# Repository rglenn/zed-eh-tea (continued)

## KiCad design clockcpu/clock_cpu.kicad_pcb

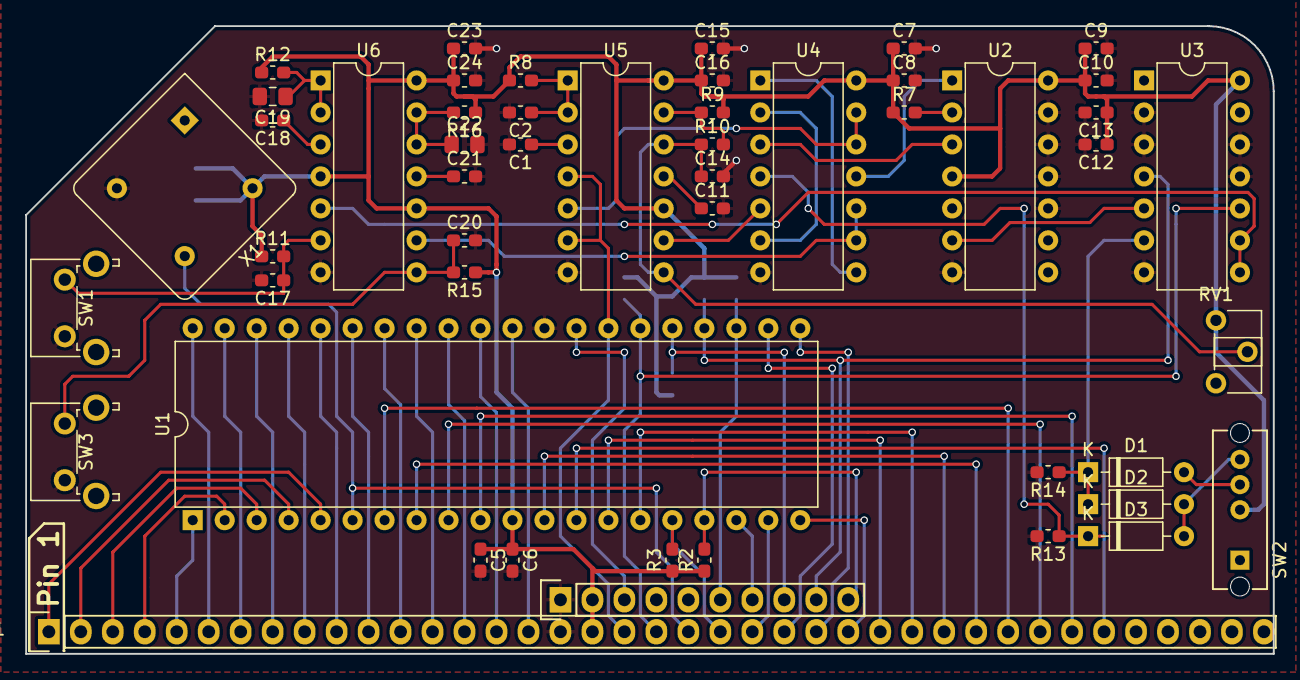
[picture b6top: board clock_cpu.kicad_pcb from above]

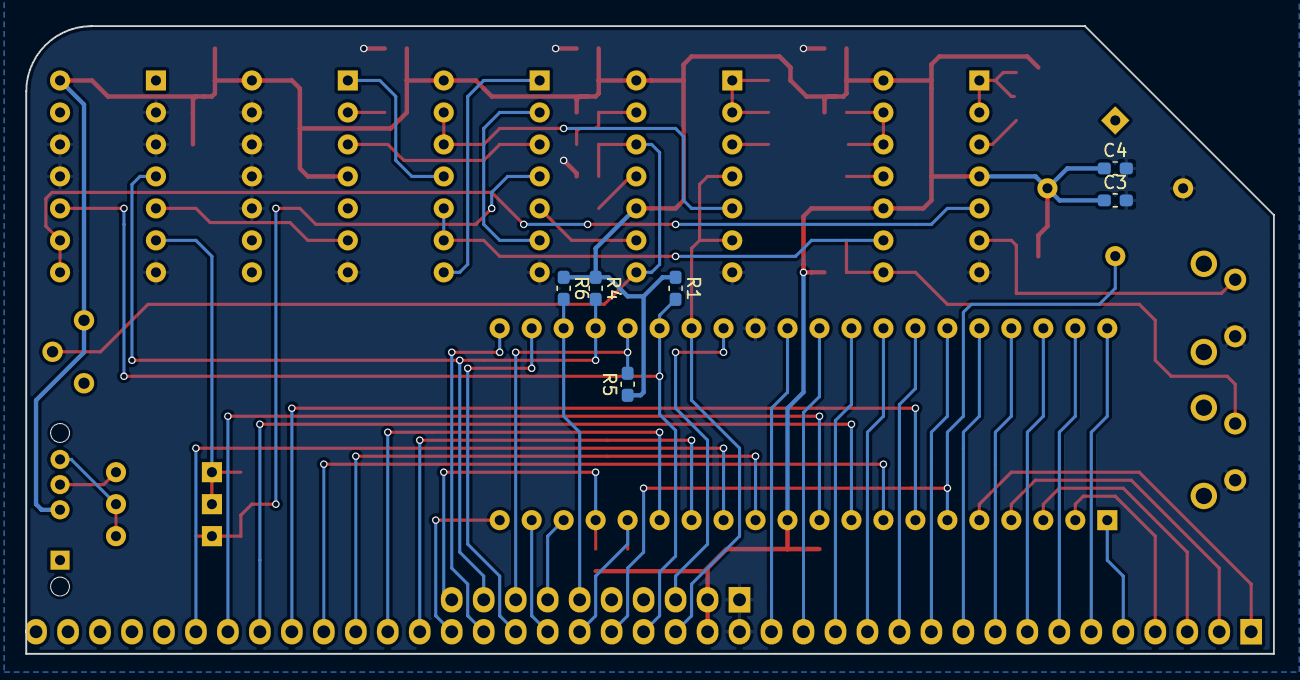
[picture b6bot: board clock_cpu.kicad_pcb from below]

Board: 2 copper layers, 99.1 x 49.9 mm, 56 parts (6 on the bottom side), 65 nets.

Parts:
C1, C2, C11, C18, C21: 10n; C_0603_1608Metric_Pad1.05x0.95mm_HandSolder
C3, C5, C7, C9, C12, C14, C15, C23: 1u; C_0603_1608Metric_Pad1.05x0.95mm_HandSolder
C4, C6, C8, C10, C13, C16, C17, C20, C24: 100n; C_0603_1608Metric_Pad1.05x0.95mm_HandSolder
C19, C22: 10u; C_0805_2012Metric_Pad1.15x1.40mm_HandSolder
D1, D2, D3: 1N4148; D_DO-35_SOD27_P7.62mm_Horizontal
J1: CONN_01X39; Pin_Header_Straight_1x39_Pitch2.54mm
J2: CONN_01X10; Pin_Header_Straight_1x10_Pitch2.54mm
R1, R2, R3, R4, R5, R6, R7, R8, R9, R10, R12, R13, R14, R16: 10K; R_0603_1608Metric_Pad1.05x0.95mm_HandSolder
R11, R15: 47K; R_0603_1608Metric_Pad1.05x0.95mm_HandSolder
RV1: 500K; Potentiometer_Piher_PT-6-H_Horizontal
SW1, SW3: SW_Push; SW_Tactile_SPST_Angled_PTS645Vx31-2LFS
SW2: SW_SP3T; OS103011MA7QP1
U1: Z80CPU; DIP-40_W15.24mm
U2: 74HCT74; DIP-14_W7.62mm
U3: 74HCT01; DIP-14_W7.62mm
U4: 74AHCT132; DIP-14_W7.62mm
U5, U6: LM556; DIP-14_W7.62mm
X1: CXO_DIP8; Oscillator_DIP-8

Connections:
/BUSACK: J2.6, R6.2, U1.23
/BUSREQ: J2.8, R5.2, U1.25
/ENABLE_AUTOSTEP: D3.1, R13.1, U4.4
/ENABLE_STEP: D1.1, D2.1, R14.1, U3.6
/HALT: J2.7, U1.18
/IORQ: J1.26, U1.20
/M1: J1.19, U1.27, U5.4, U5.6
/MREQ: J1.23, U1.19
/NMI: J2.10, R2.2, U1.17
/RD: J1.25, U1.21
/RFSH: J2.3, U1.28
/RST: J1.20, R1.2, U1.26, U3.10
/STEP_BTN: U4.1, U4.8
/STEP_CLK: U2.3, U4.3
/WAIT: J2.9, R4.2, U1.24, U3.4
/WR: J1.24, U1.22
A0: J1.16, U1.30
A1: J1.15, U1.31
A2: J1.14, U1.32
A3: J1.13, U1.33
A4: J1.12, U1.34
A5: J1.11, U1.35
A6: J1.10, U1.36
A7: J1.9, U1.37
A8: J1.8, U1.38
A9: J1.7, U1.39
A10: J1.6, U1.40
A11: J1.5, U1.1
A12: J1.4, U1.2
A13: J1.3, U1.3
A14: J1.2, U1.4
A15: J1.1, U1.5
CLK: J1.21, U1.6, X1.5
D0: J1.27, U1.14
D1: J1.28, U1.15
D2: J1.29, U1.12
D3: J1.30, U1.8
D4: J1.31, U1.7
D5: J1.32, U1.9
D6: J1.33, U1.10
D7: J1.34, U1.13
GND: C1.2, C2.2, C3.2, C4.2, C5.2, C6.2, C7.2, C8.2, C9.2, C10.2, C11.2, C12.2, C13.2, C14.2, C15.2, C16.2, C17.2, C18.2, C19.2, C20.2, C21.2, C22.2, C23.2, C24.2, J1.17, J2.1, R13.2, R14.2, SW1.1, SW3.1, U1.29, U2.7, U2.10, U2.11, U2.12, U2.13, U3.2, U3.3, U3.7, U3.11, U3.12, U4.7, U5.7, U6.7, X1.4
INT: J1.22, R3.2, U1.16
unnamed: C1.1, U5.3
unnamed: C2.1, R8.2, U5.1, U5.2
unnamed: C11.1, U5.11
unnamed: C14.1, R10.1, RV1.2, U5.8, U5.12
unnamed: C17.1, R11.2, SW1.2, U6.6
unnamed: C18.1, U6.3
unnamed: C19.1, R12.2, U6.1, U6.2
unnamed: C20.1, R15.2, SW3.2, U6.8
unnamed: C21.1, U6.11
unnamed: C22.1, R16.2, U6.12, U6.13
unnamed: D1.2, SW2.2
unnamed: D2.2, D3.2, SW2.4
unnamed: R7.2, U2.2
unnamed: R9.1, R10.2, U5.13
unnamed: U2.1, U4.11
unnamed: U2.6, U3.5
unnamed: U3.8, U3.9, U6.5
unnamed: U4.2, U4.6
unnamed: U4.5, U5.9
unnamed: U4.9, U4.10, U6.9
unnamed: U4.12, U4.13, U5.5
VCC: C3.1, C4.1, C5.1, C6.1, C7.1, C8.1, C9.1, C10.1, C12.1, C13.1, C15.1, C16.1, C23.1, C24.1, J1.18, J2.2, R1.1, R2.1, R3.1, R4.1, R5.1, R6.1, R7.1, R8.1, R9.2, R11.1, R12.1, R15.1, R16.1, RV1.1, SW2.3, U1.11, U2.4, U2.14, U3.14, U4.14, U5.10, U5.14, U6.4, U6.10, U6.14, X1.8

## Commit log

2020-07-14 Adding files so far
2020-07-14 Adding template card
2020-07-15 Adding I2C board
2020-07-17 Adding 16C550 board
2020-07-18 Started working on a 6522 board, but sounds like that might be more trouble than it's worth.
2021-01-01 Fixing schematic errors. With these fixes, the thing actually boots.
2021-02-24 Even with the most recent updates, ~M1 and IOREQ were crossed. Fixed on PCBs here, fixed with wire on the boards I have.
